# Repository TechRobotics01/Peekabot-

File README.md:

# Peekabot-
Peekabot is a esp32 based spy /surveillance camera system it is accessible from anywhere in the world (as long as it is connected to wifi) and it is accessed through telegram bot..

# REASON FOR BUILDING THIS 
why was this made you may ask well i previousely made a esp32 spy camera but it was based on wifi and it didn't have that long of a range also it was not battery operated and no custom pcb or any BMS so i made this and this project has all what the previous one lacked  
# LOGIC 
1. powers on 
2. searches for saved wifi
3. connects to wifi
4. connects to telegram bot via generated API key
5. bot starts
6. checks for incoming commands
7. returns output based on the input

# COMMANDS
1. "/start" to start the bot 
2. "/photo" to capture and send the image
3. "/flash on" to turn on the flash
4. "/flash off" to turn off the flash
5. "/quality" use this command followed by integres from 10-63 eg "/quality 20" (lower the number higher the quality)
8. "/autoflash on/off" to enable or disable the functionalty of tunring on flash automatically when taking a photo 
9. "/help" to get list of all the commands inside the bot's UI

# HARDWARE!
so this is a rough idea of what hardware will be used for this project!
1. Esp32 Ai-Thinker camera module
2. custom PCB base module with reset button and a usb port to power it easily 
3. 3d printed enclosure
4. 2x li-ion batteries

# PCB!!

so the pcb for the V1 of this project consists of 
1. IP5306 battery charging module 
2. micro usb connector 
3. battery connector
4.  header pins (to connect esp32 camera module)

the pcb has a samll form factor overall and will be powered by 2 li-ion battries which should give it a battery life of aproximately 8-12 hours which is enough for most applications furthermore you can just keep it plugged in via a micro usb port and keep it at a fixed place connect it to your wifi and not worry

Furthermore i will optimize the code so that the esp32 will go to deep sleep so that it could possibly in theory survive for months on a singular charge!! 

(update) the deepsleep is not implementable for this because deep sleep will result in turning off the wifi which will result in disconnection from the telegram api servers and the esp32 would not be able to wake up and it would remain in deep sleep
# SCHEMATICS

# 3D DESIGN!!
so the 3d design of this project is subdivided into 3 majour and minor parts 
1. the pcb enclosure case (3d part 1)
2. the pcb holder lid (3d part 2)
3. The battery holder (3d part 3)
4. 8x M2 2.2mm screws 

so basically the entire structure is made up of 3 parts one inside thich the pcb is mounted and then the lid of the same box 
then the battery are mounted under these 2 parts and this part is bigger and heavier than majority of the build...

Everything the pcb, the lid and the battery holder part are assembeled using M2 2.2mm screws which hold everything in place sturdily....

i tried to make the entire design as small ad i could but still it is bigger than expected however for the v1 of this build i just need a working prototype and i can impliment a better structure later on

## HOW TO ASSEMBLE IT ##
1. print all the parts in the 3D designs folder
2. get the pcb shipped from anywhere you can use PCBA but soldering everything yourself would be much cheaper
3. put all the SMD components for the pcb put them on the pcb with some solder paste and then put it on a hotplate and let the solder paste melt and all the smd components will be soldered in place
4. now connect 2 li-ion battery in series and solder the output wires and then add a male JST connector
5. now place the pcb in the middle piece 3d print and then screw it on using M2 allen screws
6. then connect the battery JST connector to the PCB
7. then put the esp32 camera on the PCb female header pins
8. now put all the parts together and screw it together with M2 2.2mm 10mm deep screws and refer to the exploded view.avi video for detaled instructions on where to put the screws in
9. for the software you need to log into telegram and set up a bot yourself and then you need to get the API key of the bot and then paste the API key in the code before uploading it to the camera USING AN FTDI OR BASE BASE BOARD

# EXPLODED VIEW

# ZINE PAGE!

# SOFTWARE USED 
1. arduino ide
2. fusion360
3. kicad
4. canava (for zine page)
5. brain.exe💀

## overall it features a small form factor as it is...afterall a spy/surveilance camera ##

# CREDITS
1. google.com
2. random nerd tutorials
3. arduino forms
4. instructuables
5. chatgpt/claude ai ONLY FOR DEBUGGING OF THE CODE

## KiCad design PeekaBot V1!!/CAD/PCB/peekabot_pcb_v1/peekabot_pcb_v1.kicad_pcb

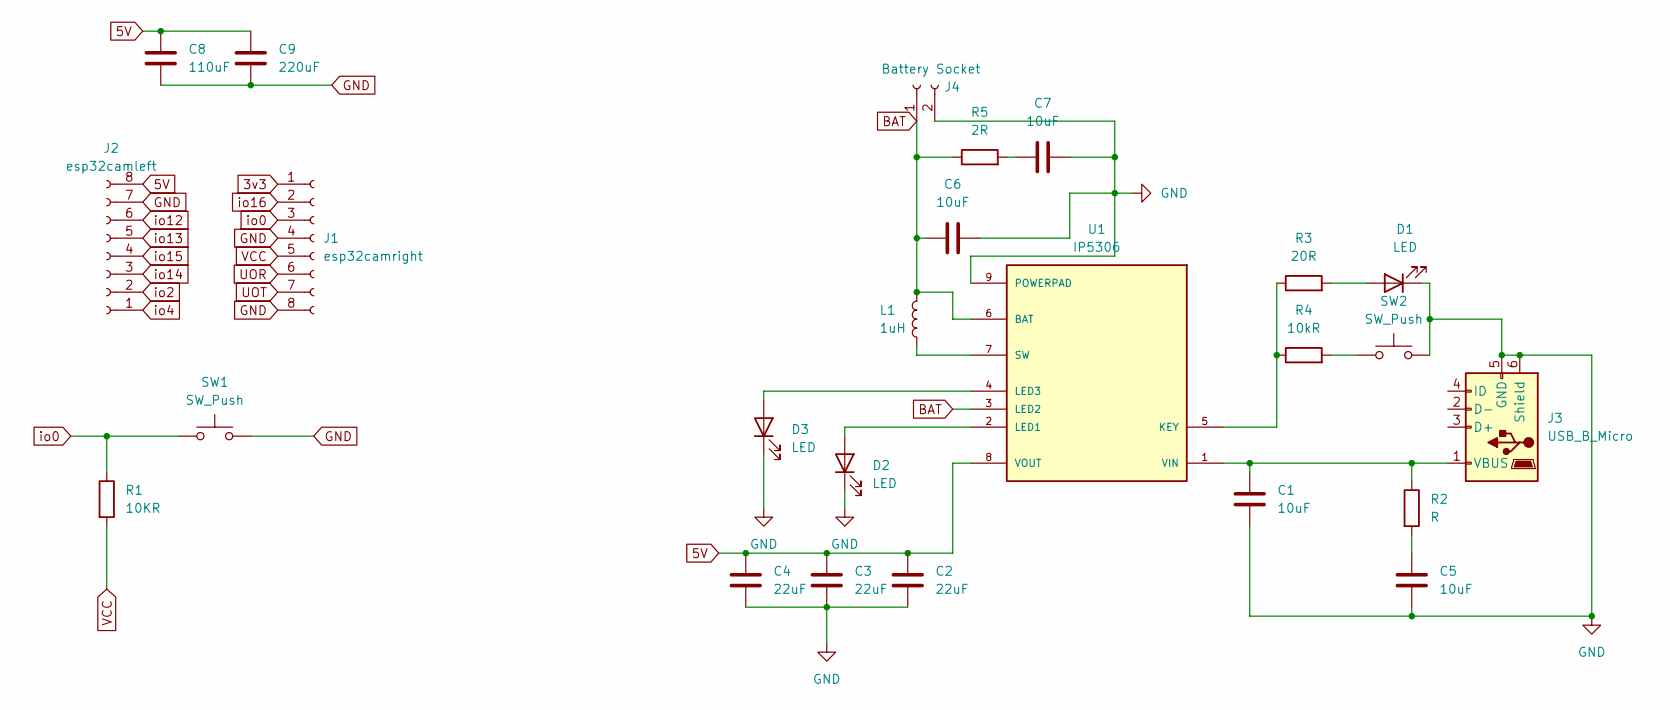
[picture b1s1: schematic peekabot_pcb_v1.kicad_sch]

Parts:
C1, C5, C6, C7: 10uF; C_0805_2012Metric
C2, C3, C4: 22uF; C_0805_2012Metric
C8: 110uF; C_0805_2012Metric
C9: 220uF; C_0805_2012Metric
D1, D2, D3: LED; LED_0805_2012Metric_Pad1.15x1.40mm_HandSolder
J1: esp32camright; PinSocket_1x08_P2.54mm_Vertical
J2: esp32camleft; PinSocket_1x08_P2.54mm_Vertical
J3: USB_B_Micro; USB_Micro-B_Molex-105017-0001
J4: Battery Socket; JST_EH_S2B-EH_1x02_P2.50mm_Horizontal
L1: 1uH; L_7.3x7.3_H3.5
R1: 10KR; R_0805_2012Metric
R2: R; R_0805_2012Metric
R3: 20R; R_0805_2012Metric
R4: 10kR; R_0805_2012Metric
R5: 2R; R_0805_2012Metric
SW1, SW2: SW_Push; SW_Push_1P1T_NO_CK_KMR2
U1: IP5306; SOP127P600X165-9N; PARTREV 1.31

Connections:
3v3: J1.1
5V: C2.1, C3.1, C4.1, C8.1, C9.1, J2.8, U1.8 (VOUT)
BAT: C6.1, J4.1, L1.2, R5.1, U1.3 (LED2), U1.6 (BAT)
GND: C1.2, C2.2, C3.2, C4.2, C5.2, C6.2, C7.2, C8.2, C9.2, D1.1 (K), D2.1 (K), D3.1 (K), J1.4, J1.8, J2.7, J3.5 (GND), J3.6 (Shield), J4.2, SW1.2, SW2.2, U1.9 (POWERPAD); also elsewhere on the board
unnamed: C5.1, R2.2
unnamed: C7.1, R5.2
unnamed: D1.2 (A), R3.2
unnamed: D2.2 (A), U1.2 (LED1)
unnamed: D3.2 (A), U1.4 (LED3)
unnamed: C1.1, J3.1 (VBUS), R2.1, U1.1 (VIN)
unnamed 10: R4.2, SW2.1; also elsewhere on the board
unnamed: R3.1, R4.1, U1.5 (KEY)
unnamed: L1.1, U1.7 (SW)
UOR: J1.6
UOT: J1.7
VCC: J1.5, R1.2
io0: J1.3, R1.1, SW1.1; also elsewhere on the board
io2: J2.2
io4: J2.1
io12: J2.6
io13: J2.5
io14: J2.3
io15: J2.4
io16: J1.2

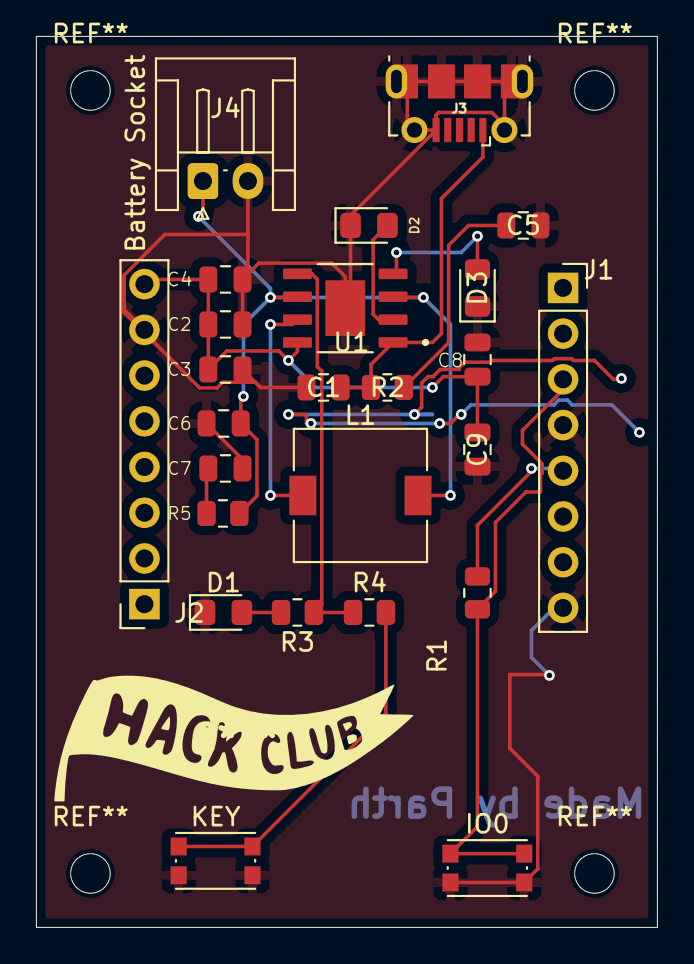
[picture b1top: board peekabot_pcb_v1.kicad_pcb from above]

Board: 2 copper layers, 34.5 x 49.5 mm, 25 parts (0 on the bottom side), 14 nets.

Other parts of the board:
IO0: SW_Push; SW_Push_1P1T_NO_CK_KMR2
KEY: SW_Push; SW_Push_1P1T_NO_CK_KMR2

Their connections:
GND: IO0.2, KEY.2; also elsewhere on the board
unnamed 10: KEY.1; also elsewhere on the board
io0: IO0.1; also elsewhere on the board

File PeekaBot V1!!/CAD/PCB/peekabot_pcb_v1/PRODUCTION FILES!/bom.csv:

Designator,Footprint,Quantity,Value,LCSC Part #
"C1, C5, C6, C7",805,4,10uF,
"C2, C3, C4",805,3,22uF,
C8,805,1,110uF,
C9,805,1,220uF,
"D1, D2, D3",805,3,LED,
"IO0, KEY",SW_Push_1P1T_NO_CK_KMR2,2,SW_Push,
J1,PinSocket_1x08_P2.54mm_Vertical,1,esp32camright,
J2,PinSocket_1x08_P2.54mm_Vertical,1,esp32camleft,
J3,USB_Micro-B_Molex-105017-0001,1,USB_B_Micro,
J4,JST_EH_S2B-EH_1x02_P2.50mm_Horizontal,1,Battery Socket,
L1,L_7.3x7.3_H3.5,1,1uH,
"R1, R4",805,2,10KR,
R2,805,1,R,
R3,805,1,20R,
R5,805,1,2R,
U1,SOP127P600X165-9N,1,IP5306,

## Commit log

2026-04-05 Developed code for Peekabot camera
2026-04-06 STARTED WORK ON THE PCB SCHEMATICS FOR THE BASEBOARD OF ESP32
2026-04-08 started working on the schematics of the pcb
2026-04-09 UPDATED PCB-MARK-1!!!
2026-04-11 PCB AND 3D DESIGN WORK
    started 3d printable enclosure design for the project and corrected a majour spacing error in the PCB
2026-04-12 updated 3d enclosure files
2026-04-14 UPDATED AND IMPROVED CODE
2026-04-14 Upodated code,3d desig,pcb
    improved the code
    improved and iterated the 3d design
    rendered all the 3d parts
    added name and hack club logo in the pcb
    organized all the file
2026-04-15 Created BOM
2026-04-17 FINALIZED BOM
2026-04-18 created zine page and updated BOM
2026-04-18 made changes in zine page
2026-04-18 updated zine,bom,code
2026-04-23 added more cad files
2026-04-23 update name of bom file
2026-06-01 updated bom and cad stuff
2026-06-03 peekabot updates
